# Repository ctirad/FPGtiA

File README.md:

# FPGtiA
Atari 8bit GTIA chip recreation with VGA and HDMI/DVI output

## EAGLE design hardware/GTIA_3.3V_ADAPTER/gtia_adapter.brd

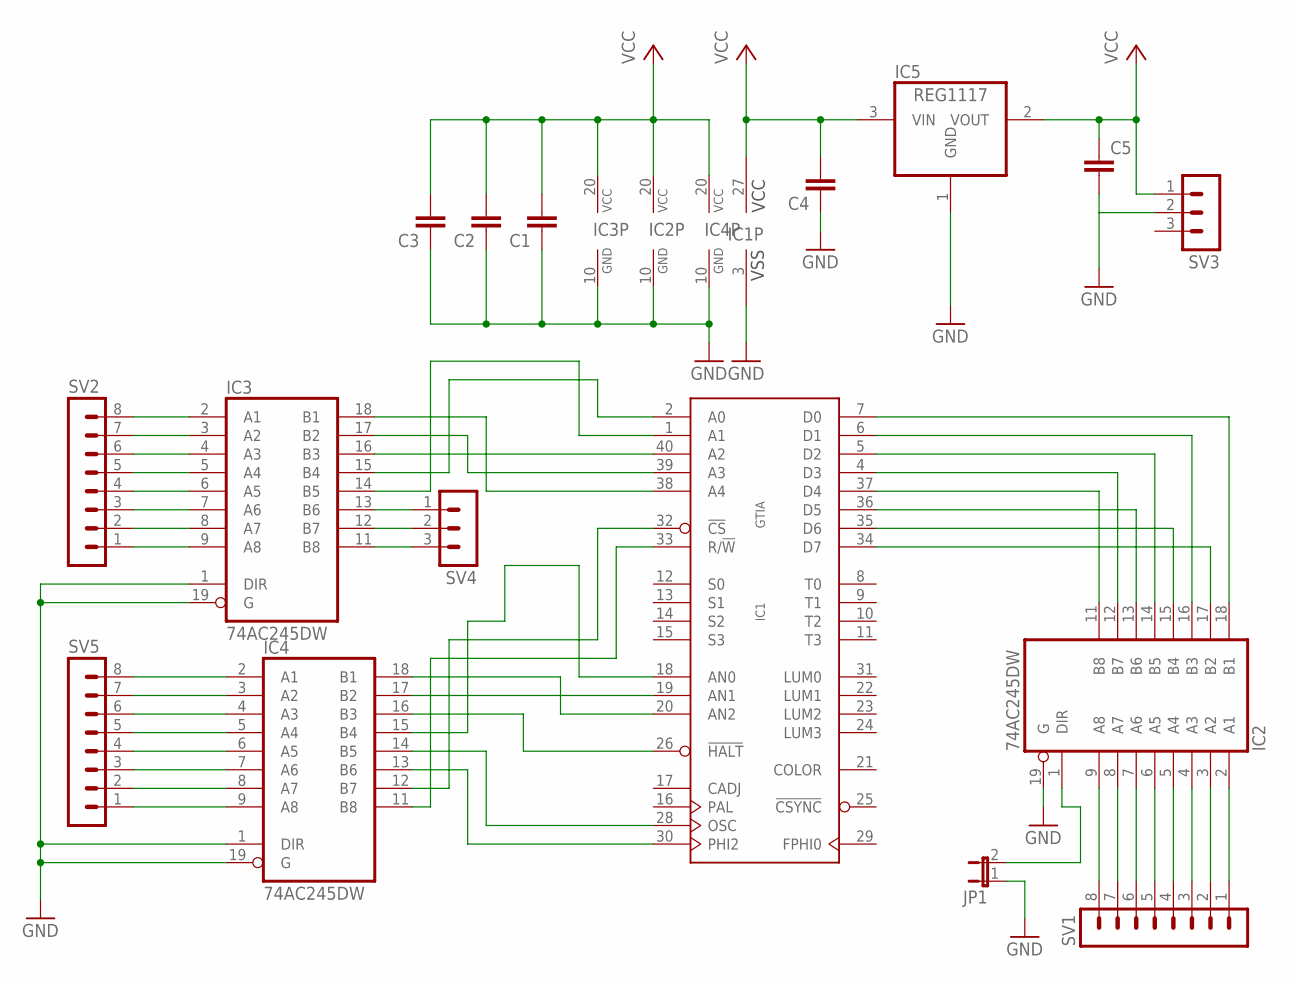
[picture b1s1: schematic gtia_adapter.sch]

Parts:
C1, C2, C3, C4, C5: C-EUC1206; C1206
IC1: GTIA; DIL40
IC2, IC3, IC4: 74AC245DW; SO20W
IC5: REG1117; SOT223
JP1: JP1E; JP1
SV1, SV2, SV5: MA08-1
SV3, SV4: MA03-1

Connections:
3.3V_VCC: C1.2, C2.2, C3.2, C5.1, IC2.20 (VCC), IC3.20 (VCC), IC4.20 (VCC), IC5.2 (VOUT), SV3.1
5V_VCC: C4.2, IC1.27 (VCC), IC5.3 (VIN)
GND: C1.1, C2.1, C3.1, C4.1, C5.2, IC1.3 (VSS), IC2.10 (GND), IC2.19 (G), IC3.1 (DIR), IC3.10 (GND), IC3.19 (G), IC4.1 (DIR), IC4.10 (GND), IC4.19 (G), IC5.1 (GND), JP1.1, SV3.2
unnamed: IC1.18 (AN0), IC4.15 (B4)
unnamed: IC1.19 (AN1), IC4.17 (B2)
unnamed: IC1.20 (AN2), IC4.18 (B1)
unnamed: IC1.2 (A0), IC3.15 (B4)
unnamed: IC1.1 (A1), IC3.14 (B5)
unnamed: IC1.7 (D0), IC2.18 (B1)
unnamed: IC1.6 (D1), IC2.16 (B3)
unnamed: IC1.35 (D6), IC2.15 (B4)
unnamed: IC1.36 (D5), IC2.13 (B6)
unnamed: IC1.4 (D3), IC2.12 (B7)
unnamed: IC1.5 (D2), IC2.14 (B5)
unnamed: IC1.39 (A3), IC3.17 (B2)
unnamed: IC1.37 (D4), IC2.11 (B8)
unnamed: IC1.40 (A2), IC3.16 (B3)
unnamed: IC2.2 (A1), SV1.1
unnamed: IC2.3 (A2), SV1.2
unnamed: IC1.33 (R/!W), IC4.11 (B8)
unnamed: IC1.32 (!CS), IC4.12 (B7)
unnamed: IC2.4 (A3), SV1.3
unnamed: IC1.26 (!HALT), IC4.16 (B3)
unnamed: IC2.5 (A4), SV1.4
unnamed: IC2.6 (A5), SV1.5
unnamed: IC2.7 (A6), SV1.6
unnamed: IC2.8 (A7), SV1.7
unnamed: IC2.9 (A8), SV1.8
unnamed: IC1.38 (A4), IC3.18 (B1)
unnamed: IC3.13 (B6), SV4.1
unnamed: IC1.34 (D7), IC2.17 (B2)
unnamed: IC3.12 (B7), SV4.2
unnamed: IC3.11 (B8), SV4.3
unnamed: IC3.2 (A1), SV2.8
unnamed: IC3.3 (A2), SV2.7
unnamed: IC3.4 (A3), SV2.6
unnamed: IC3.5 (A4), SV2.5
unnamed: IC3.6 (A5), SV2.4
unnamed: IC1.28 (OSC), IC4.14 (B5)
unnamed: IC1.30 (PHI2), IC4.13 (B6)
unnamed: IC3.7 (A6), SV2.3
unnamed: IC3.8 (A7), SV2.2
unnamed: IC3.9 (A8), SV2.1
unnamed: IC4.2 (A1), SV5.8
unnamed: IC4.3 (A2), SV5.7
unnamed: IC4.4 (A3), SV5.6
unnamed: IC4.5 (A4), SV5.5
unnamed: IC4.6 (A5), SV5.4
unnamed: IC4.7 (A6), SV5.3
unnamed: IC4.8 (A7), SV5.2
unnamed: IC4.9 (A8), SV5.1
unnamed: IC2.1 (DIR), JP1.2

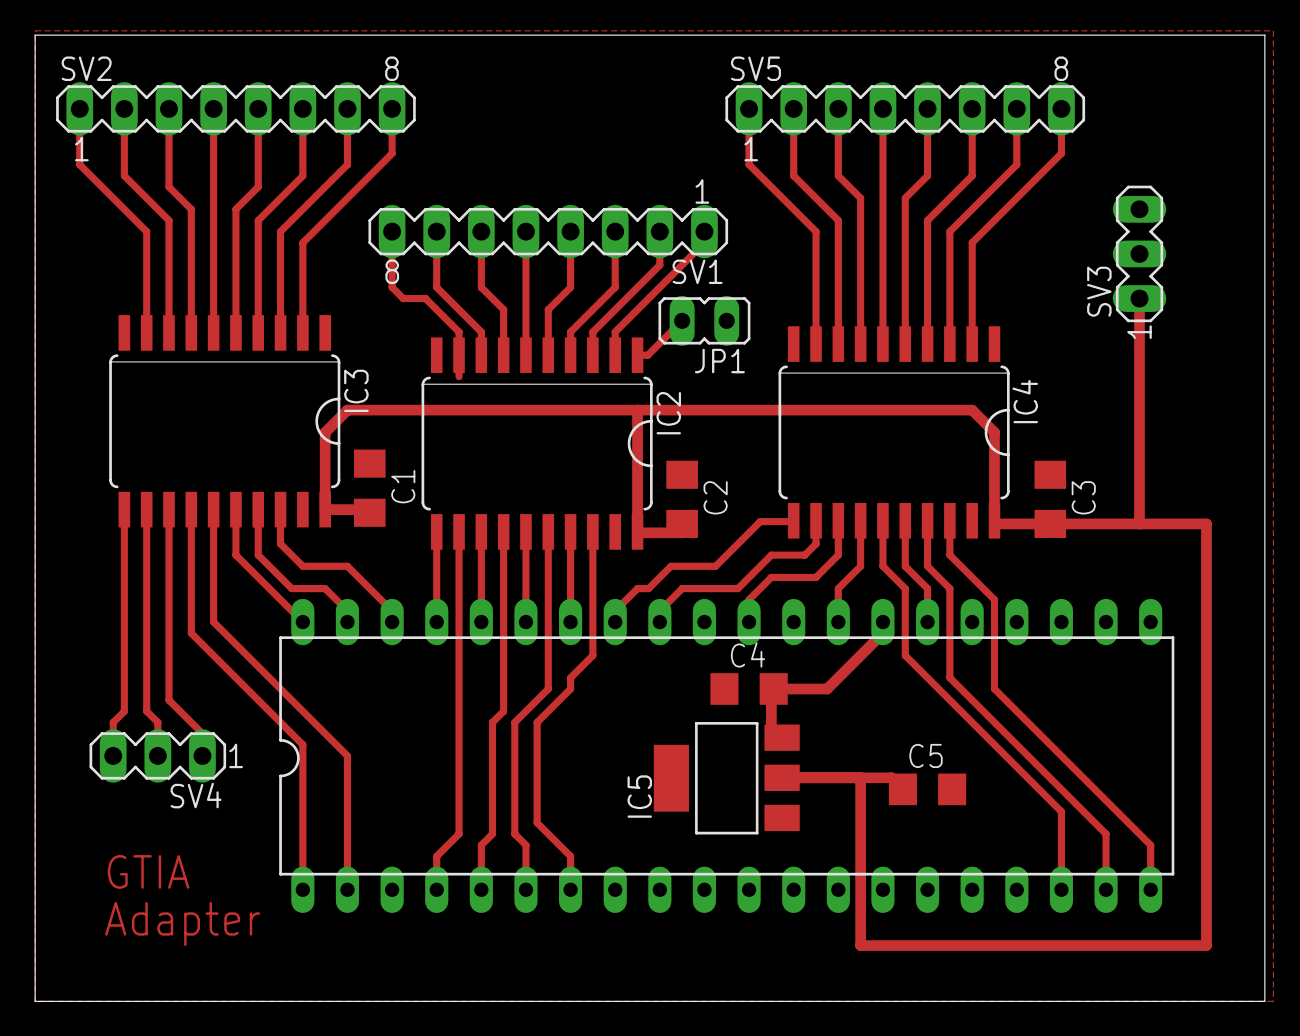
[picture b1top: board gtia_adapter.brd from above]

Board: 2 copper layers, 70.0 x 55.0 mm, 16 parts (0 on the bottom side), 52 nets.

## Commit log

2017-02-03 3.3V level shifter added

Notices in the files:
parts and their libraries:
eagle-6.5.0-atari: Copyright (c) 2010
Copyright (c) 2009
This library is licensed under the
Creative Commons Attribution 3.0 United States License.
